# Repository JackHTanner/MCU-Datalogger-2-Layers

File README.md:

# MCU Datalogger 
A 2 and 4-layer version of MCU Datalogger PCB that was designed in KiCAD.

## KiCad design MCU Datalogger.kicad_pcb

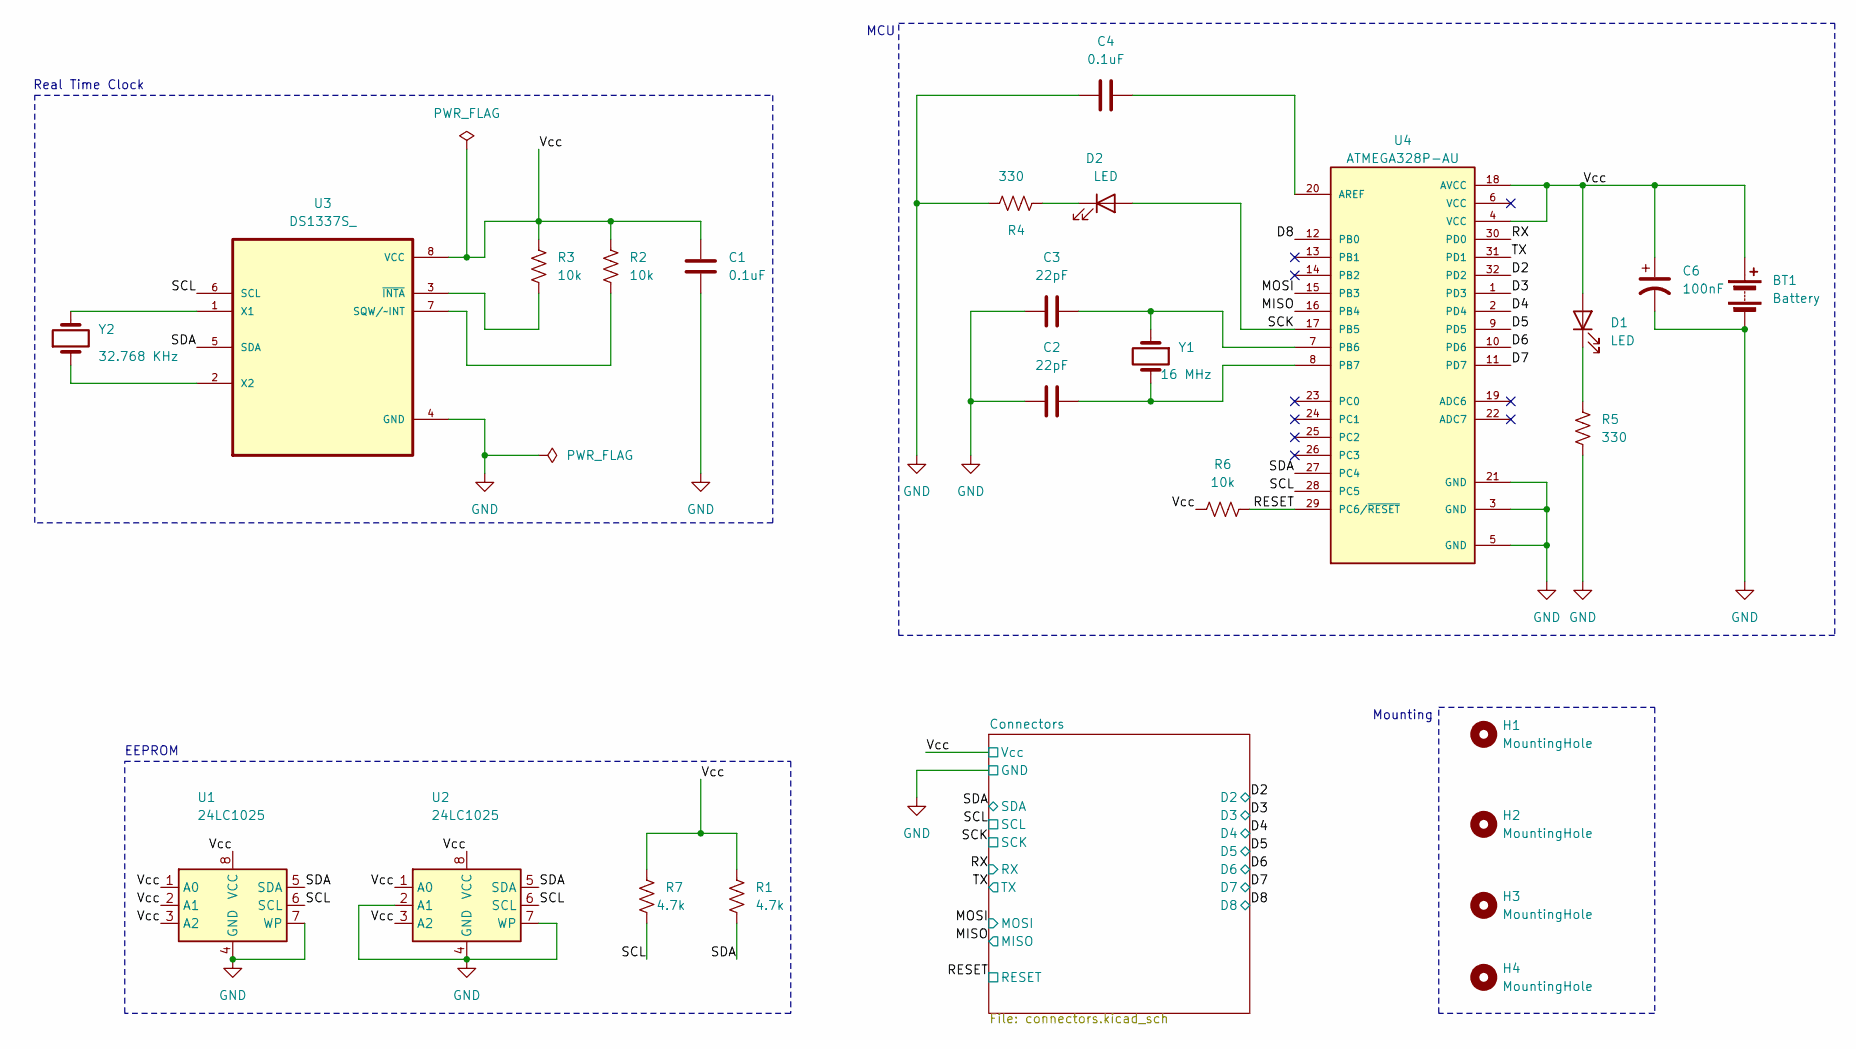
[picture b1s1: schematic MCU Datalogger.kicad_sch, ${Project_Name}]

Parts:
BT1: Battery; PinHeader_1x02_P2.54mm_Vertical
C1, C4: 0.1uF; C_0805_2012Metric
C2, C3: 22pF; C_0805_2012Metric
C6: 100nF; C_0805_2012Metric
D1, D2: LED; LED_0805_2012Metric
H1, H2, H3, H4: MountingHole; MountingHole_2.1mm
R1, R7: 4.7k; R_0805_2012Metric
R2, R3, R6: 10k; R_0805_2012Metric
R4, R5: 330; R_0805_2012Metric
U1, U2: 24LC1025; SOIC-8_5.23x5.23mm_P1.27mm
U3: DS1337S_; SOIC127P600X175-8N
U4: ATMEGA328P-AU; QFP80P900X900X120-32N; PARTREV 8271A
Y1: 16 MHz; Crystal_SMD_5032-2Pin_5.0x3.2mm_HandSoldering
Y2: 32.768 KHz; Crystal_SMD_5032-2Pin_5.0x3.2mm_HandSoldering

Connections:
/D2: U4.32 (PD2); also elsewhere on the board
/D3: U4.1 (PD3); also elsewhere on the board
/D4: U4.2 (PD4); also elsewhere on the board
/D5: U4.9 (PD5); also elsewhere on the board
/D6: U4.10 (PD6); also elsewhere on the board
/D7: U4.11 (PD7); also elsewhere on the board
/D8: U4.12 (PB0); also elsewhere on the board
/MISO: U4.16 (PB4); also elsewhere on the board
/MOSI: U4.15 (PB3); also elsewhere on the board
/RESET: R6.2, U4.29 (PC6/~RESET); also elsewhere on the board
/RX: U4.30 (PD0); also elsewhere on the board
/SCK: D2.2 (A), U4.17 (PB5); also elsewhere on the board
/SCL: R7.1, U1.6 (SCL), U2.6 (SCL), U3.6 (SCL), U4.28 (PC5); also elsewhere on the board
/SDA: R1.2, U1.5 (SDA), U2.5 (SDA), U3.5 (SDA), U4.27 (PC4); also elsewhere on the board
/TX: U4.31 (PD1); also elsewhere on the board
/Vcc: BT1.1 (+), C1.1, C6.1, D1.2 (A), R1.1, R2.1, R3.1, R6.1, R7.2, U1.1 (A0), U1.2 (A1), U1.3 (A2), U1.8 (VCC), U2.1 (A0), U2.3 (A2), U2.8 (VCC), U3.8 (VCC), U4.4 (VCC), U4.18 (AVCC); also elsewhere on the board
GND: BT1.2 (-), C1.2, C2.1, C3.1, C4.1, C6.2, R4.2, R5.2, U1.4 (GND), U1.7 (WP), U2.2 (A1), U2.4 (GND), U2.7 (WP), U3.4 (GND), U4.3 (GND), U4.5 (GND), U4.21 (GND); also elsewhere on the board
unnamed: D1.1 (K), R5.1
unnamed: D2.1 (K), R4.1
unnamed: R2.2, U3.7 (SQW/~INT)
unnamed: U3.1 (X1), Y2.2
unnamed: U3.2 (X2), Y2.1
unnamed: R3.2, U3.3 (~INTA)
unnamed: C4.2, U4.20 (AREF)
unnamed: C3.2, U4.7 (PB6), Y1.1
unnamed: C2.2, U4.8 (PB7), Y1.2

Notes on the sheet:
MCU
Mounting
EEPROM
Real Time Clock

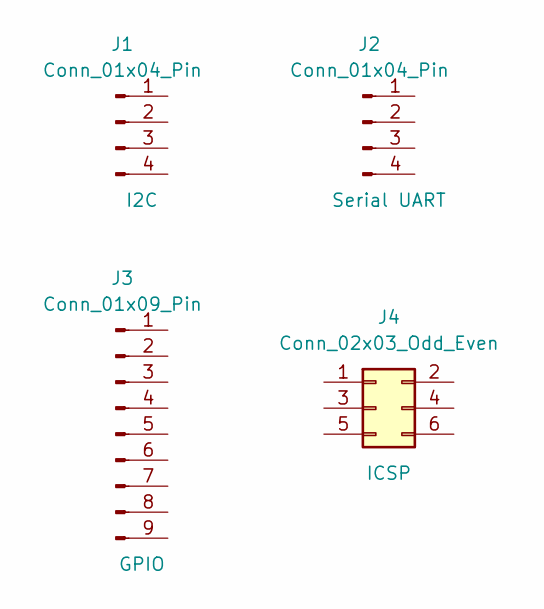
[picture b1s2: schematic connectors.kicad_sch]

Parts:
J1, J2: Conn_01x04_Pin
J3: Conn_01x09_Pin
J4: Conn_02x03_Odd_Even

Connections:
/D2: J3.1; also elsewhere on the board
/D3: J3.2; also elsewhere on the board
/D4: J3.3; also elsewhere on the board
/D5: J3.4; also elsewhere on the board
/D6: J3.5; also elsewhere on the board
/D7: J3.6; also elsewhere on the board
/D8: J3.7; also elsewhere on the board
/MISO: J4.1; also elsewhere on the board
/MOSI: J4.4; also elsewhere on the board
/RESET: J4.5; also elsewhere on the board
/RX: J2.3; also elsewhere on the board
/SCK: J4.3; also elsewhere on the board
/SCL: J1.4; also elsewhere on the board
/SDA: J1.3; also elsewhere on the board
/TX: J2.4; also elsewhere on the board
/Vcc: J1.2, J2.2, J3.9, J4.2; also elsewhere on the board
GND: J1.1, J2.1, J3.8, J4.6; also elsewhere on the board

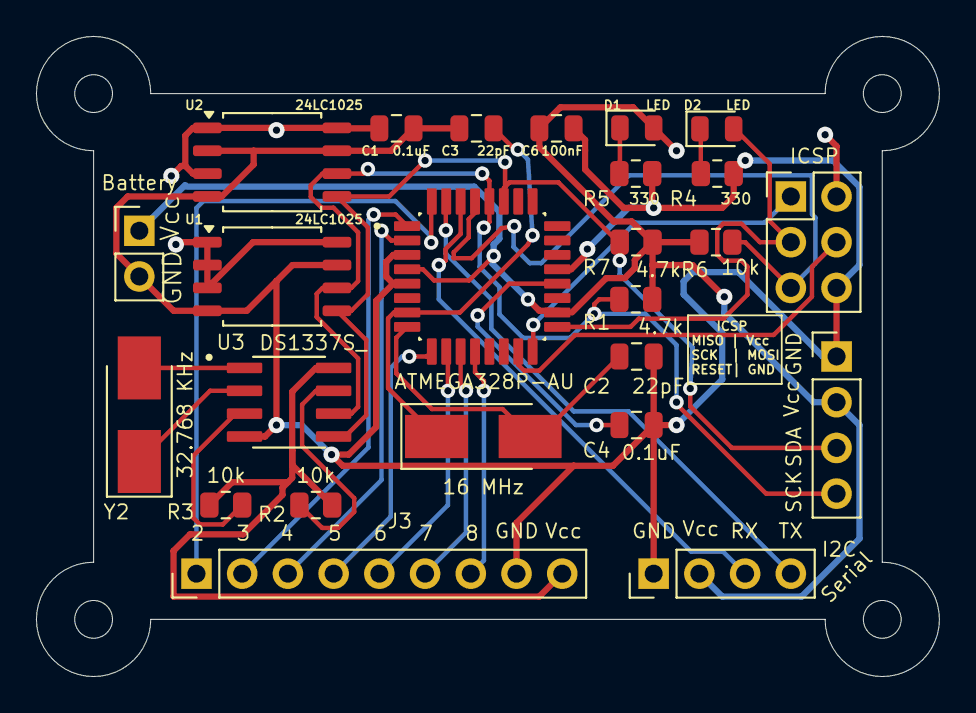
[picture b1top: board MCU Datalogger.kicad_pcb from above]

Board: 2 copper layers, 50.2 x 35.6 mm, 29 parts (0 on the bottom side), 26 nets.

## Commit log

2024-12-29 First commit.
2024-12-29 Setup of EESchema for new project.
2024-12-29 Have added required symbols to schematic sheets.
2024-12-29 Changed locations of symbols (arrange).
2024-12-29 Added component values.
2024-12-29 Completed symbol-footprint associations.
2024-12-30 Completed wiring of main sheet.
2024-12-30 Completed wiring and ERC. Fixed some issues.
2024-12-30 Allocated GND and Vcc nets to Ground and Power net classes.
2024-12-30 Completed comments and organization in schematic.
2024-12-30 Setup PCBNew.
2024-12-30 Completed placement of footprints in PCBNew.
2024-12-30 Routing except GND and Vcc complete + changed edge cuts surrounding mounting holes.
2024-12-30 Refined routing complete.
2024-12-30 Fixed outstanding issues and set Silkscreen.
2024-12-30 Fixed defects relating to SCL/SCK confusion.
2024-12-30 Added gitattributes.
2024-12-30 Fixed 2 layer PCB regarding SCL/SCK issues.
2024-12-30 Completed 2-Layer PCB Project.
2024-12-30 Completed 2 Layer PCB.
2024-12-30 Added gerber directories to .gitignore.
2024-12-30 Completed 4 Layer PCB Routing.
2024-12-30 Added board characteristics.
2025-01-01 Added /Gerbers to .gitignore.
2025-01-01 Random changes for experimentation.
2025-01-01 Added footprints.
2025-01-01 Resolved conflict in .gitattributes
2025-01-01 Deleted auto_saved_files.
2025-01-01 Changed back some experiments.
2025-01-12 Create README.md
    Created README for MCU Datalogger explaining what this project is.
